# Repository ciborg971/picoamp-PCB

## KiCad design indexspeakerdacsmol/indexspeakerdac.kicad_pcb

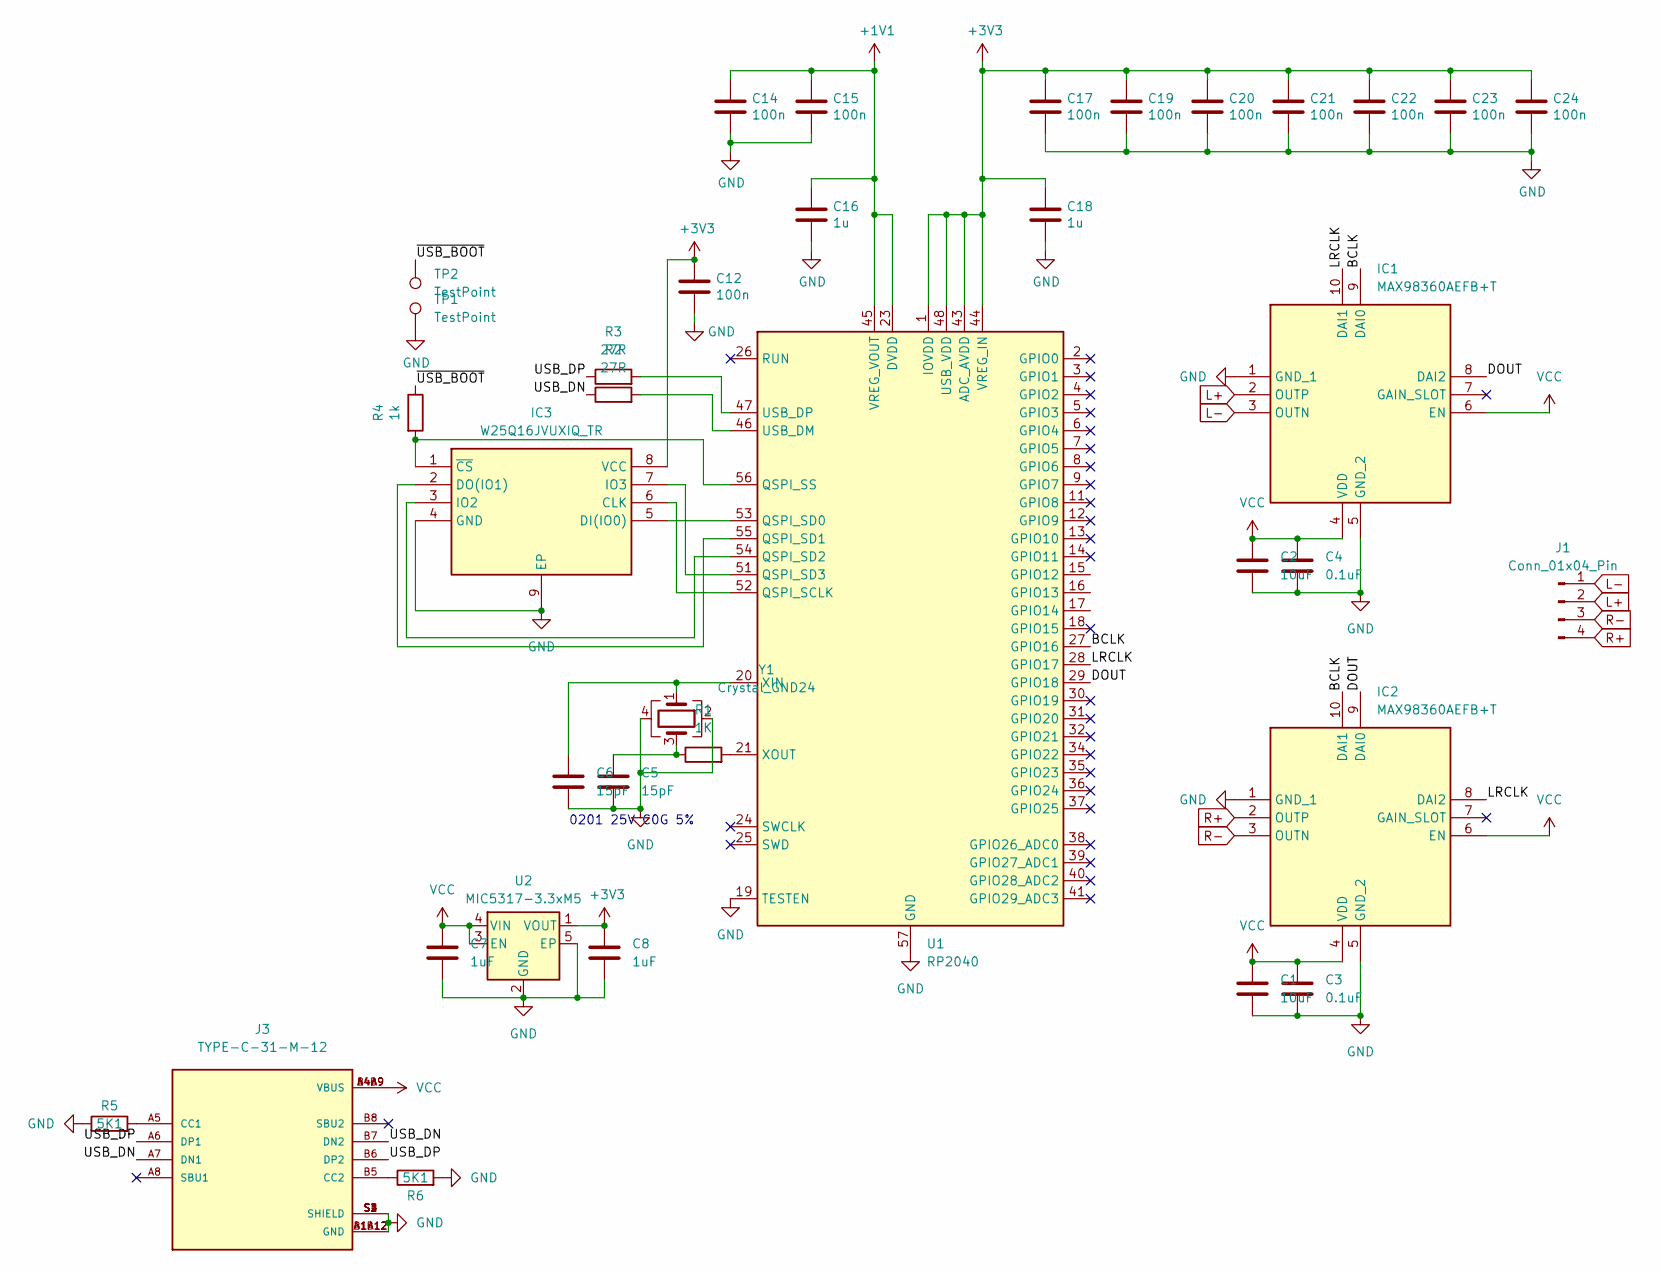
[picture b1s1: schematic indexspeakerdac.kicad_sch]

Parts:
C1, C2: 10uF; C_0603_1608Metric
C3, C4: 0.1uF; C_0402_1005Metric
C5, C6: 15pF; C_0201_0603Metric
C7, C8: 1uF; C_0402_1005Metric
C12, C14, C15, C17, C19, C20, C21, C22, C23, C24: 100n; C_0201_0603Metric
C16, C18: 1u; C_0402_1005Metric
IC1, IC2: MAX98360AEFB+T; MAX98360AEFB; Mouser Part Number 700-MAX98360AEFB+T
IC3: W25Q16JVUXIQ_TR; SON50P300X200X60-9N; Mouser Part Number 454-W25Q16JVUXIQTR
J1: Conn_01x04_Pin; PinHeader_1x04_P2.00mm_Horizontal
J3: TYPE-C-31-M-12; HRO_TYPE-C-31-M-12; PARTREV A; LCSC C165948
R1: 1K; R_0402_1005Metric
R2, R3: 27R; R_0201_0603Metric
R4: 1k; R_0201_0603Metric
R5, R6: 5K1; R_0201_0603Metric; LCSC C274341
TP1, TP2: TestPoint; TestPoint_Pad_1.0x1.0mm
U1: RP2040; QFN-56-1EP_7x7mm_P0.4mm_EP3.2x3.2mm
U2: MIC5317-3.3xM5; UDFN-4-1EP_1x1mm_P0.65mm_EP0.48x0.48mm
Y1: Crystal_GND24; Crystal_SMD_3225-4Pin_3.2x2.5mm

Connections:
+1V1: C14.1, C15.1, C16.1, U1.23 (DVDD), U1.45 (VREG_VOUT), U1.50 (DVDD)
+3V3: C8.1, C12.1, C17.1, C18.1, C19.1, C20.1, C21.1, C22.1, C23.1, C24.1, IC3.8 (VCC), U1.1 (IOVDD), U1.10 (IOVDD), U1.22 (IOVDD), U1.33 (IOVDD), U1.42 (IOVDD), U1.43 (ADC_AVDD), U1.44 (VREG_IN), U1.48 (USB_VDD), U1.49 (IOVDD), U2.1 (VOUT)
/BCLK: IC1.9 (DAI0), IC2.10 (DAI1), U1.27 (GPIO16)
/DOUT: IC1.8 (DAI2), IC2.9 (DAI0), U1.29 (GPIO18)
/LRCLK: IC1.10 (DAI1), IC2.8 (DAI2), U1.28 (GPIO17)
/USB_DN: J3.A7 (DN1), J3.B7 (DN2), R2.1
/USB_DP: J3.A6 (DP1), J3.B6 (DP2), R3.1
/~USB_BOOT: R4.1, TP2.1
GND: C1.2, C2.2, C3.2, C4.2, C5.2, C6.2, C7.2, C8.2, C12.2, C14.2, C15.2, C16.2, C17.2, C18.2, C19.2, C20.2, C21.2, C22.2, C23.2, C24.2, IC1.1 (GND_1), IC1.5 (GND_2), IC2.1 (GND_1), IC2.5 (GND_2), IC3.4 (GND), IC3.9 (EP), J3.A1B12 (GND), J3.B1A12 (GND), J3.S1 (SHIELD), J3.S2 (SHIELD), J3.S3 (SHIELD), J3.S4 (SHIELD), R5.1, R6.2, TP1.1, U1.19 (TESTEN), U1.57 (GND), U2.2 (GND), U2.5 (EP), Y1.2, Y1.4
L+: IC1.2 (OUTP), J1.2
L-: IC1.3 (OUTN), J1.1
unnamed: C5.1, R1.1, Y1.3
unnamed: IC3.6 (CLK), U1.52 (QSPI_SCLK)
unnamed: IC3.5 (DI(IO0)), U1.53 (QSPI_SD0)
unnamed: IC3.2 (DO(IO1)), U1.55 (QSPI_SD1)
unnamed: IC3.3 (IO2), U1.54 (QSPI_SD2)
unnamed: IC3.7 (IO3), U1.51 (QSPI_SD3)
unnamed: IC3.1 (~CS), R4.2, U1.56 (QSPI_SS)
unnamed: J3.A5 (CC1), R5.2
unnamed: J3.B5 (CC2), R6.1
unnamed: R2.2, U1.46 (USB_DM)
unnamed: R3.2, U1.47 (USB_DP)
unnamed: C6.1, U1.20 (XIN), Y1.1
unnamed: R1.2, U1.21 (XOUT)
R+: IC2.2 (OUTP), J1.4
R-: IC2.3 (OUTN), J1.3
VCC: C1.1, C2.1, C3.1, C4.1, C7.1, IC1.4 (VDD), IC1.6 (EN), IC2.4 (VDD), IC2.6 (EN), J3.A4B9 (VBUS), J3.B4A9 (VBUS), U2.3 (EN), U2.4 (VIN)

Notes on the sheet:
0201 25V C0G 5%

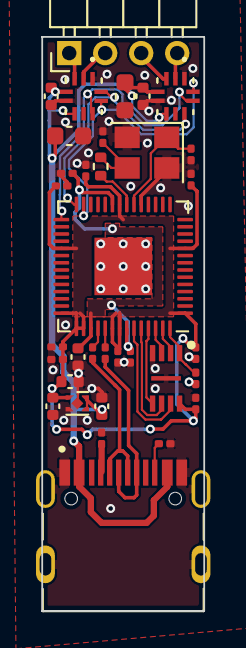
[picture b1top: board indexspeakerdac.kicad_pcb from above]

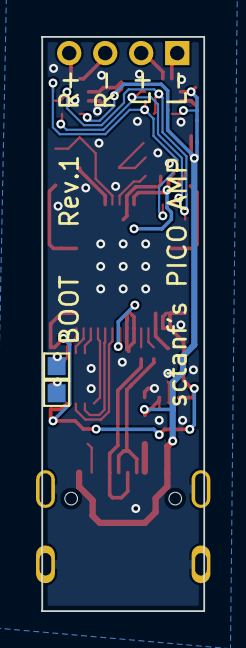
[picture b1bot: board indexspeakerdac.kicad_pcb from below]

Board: 2 copper layers, 9.0 x 31.9 mm, 36 parts (2 on the bottom side), 27 nets.

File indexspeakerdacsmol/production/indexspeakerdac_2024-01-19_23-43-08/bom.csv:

Designator,Footprint,Quantity,Value,LCSC Part #
"C1, C2",0603,2,10uF,
"C12, C14, C15, C17, C19, C20, C21, C22, C23, C24",0201,10,100n,
"C16, C18",0402,2,1u,
"C3, C4",0402,2,0.1uF,
"C5, C6",0201,2,15pF,
"C7, C8",0402,2,1uF,
"IC1, IC2",MAX98360AEFB,2,MAX98360AEFB+T,
IC3,SON50P300X200X60-9N,1,W25Q16JVUXIQ_TR,
J1,PinHeader_1x04_P2.00mm_Horizontal,1,Conn_01x04_Pin,
J3,HRO_TYPE-C-31-M-12,1,TYPE-C-31-M-12,C165948
R1,0402,1,1K,
"R2, R3",0201,2,27R,
R4,0201,1,1k,
"R5, R6",0201,2,5K1,C105872
"TP1, TP2",TestPoint_Pad_1.0x1.0mm,2,TestPoint,
U1,QFN-56-1EP_7x7mm_P0.4mm_EP3.2x3.2mm,1,RP2040,
U2,UDFN-4-1EP_1x1mm_P0.65mm_EP0.48x0.48mm,1,MIC5317-3.3xM5,
Y1,Crystal_SMD_3225-4Pin_3.2x2.5mm,1,Crystal_GND24,

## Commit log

2024-01-19 add usb c + bom
2024-01-19 production files for jlcpcb
